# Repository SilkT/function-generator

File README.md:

# function-generator
A function generator with variable frequency and different typical signals to choose from(sine, triangle, saw and square).
the project is based on STM32F051K8 microcontroller which features built-in DAC. Shematics and layout were designed using Autodesk Eagle software. For the most part shematics were designed according to datasheets of used components. The resulting analog signal is ‘cleaned’ from high frequency component with calculated passive low-pass filter.
Software part of the project was executed in C using STM32Cube for configuration and Keil µVision as IDE. Project uses standard HAL drivers and own code for digital-to-analog processing with wavetables generated in Matlab, that are converted to analog values on the output of device. Modified OpenSource library is used for indication on the OLED screen.
Software still needs a lot of tuning, but that's just a part of a bigger project involving DSP on low-end STM32 MCUs so I'm working on it ;)

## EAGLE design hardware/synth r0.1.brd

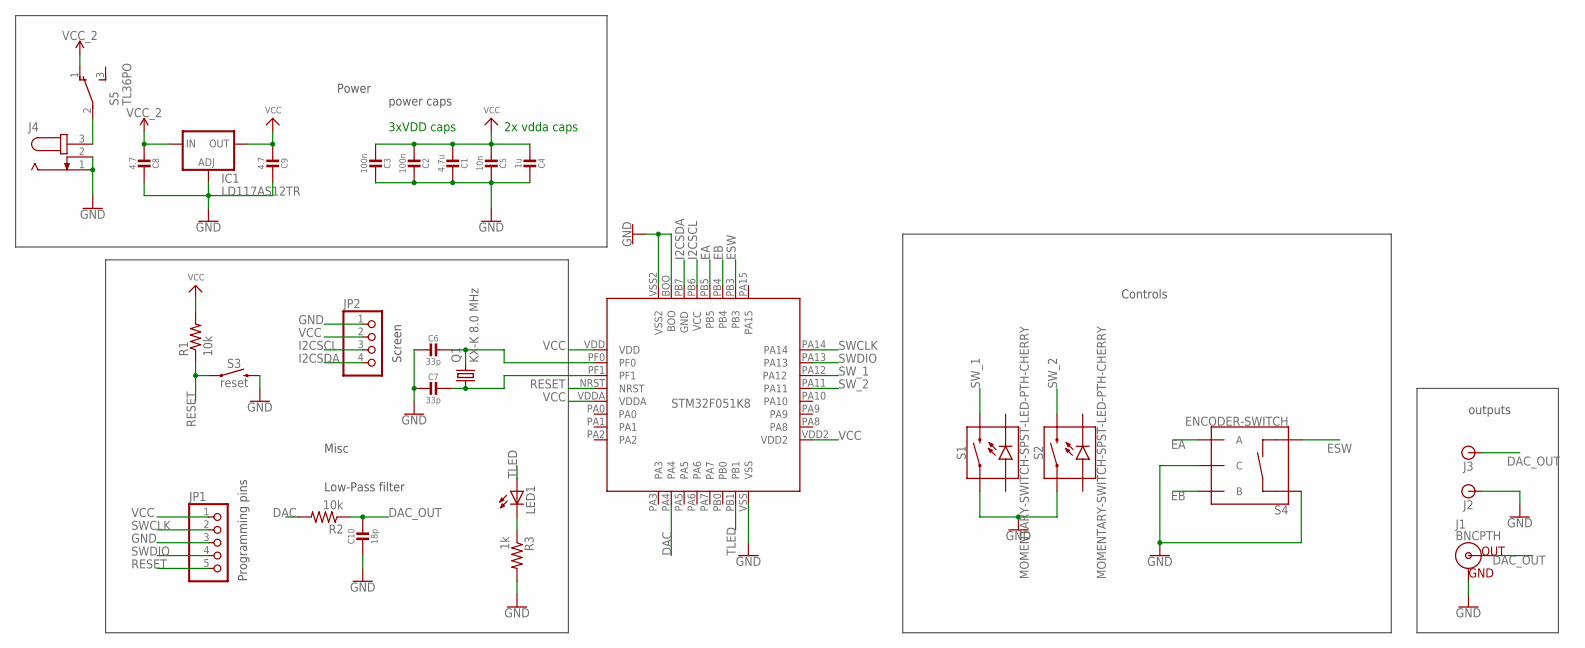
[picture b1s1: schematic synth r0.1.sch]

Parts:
C1: 4.7u; 0805-NO
C2, C3: 100n; 0805-NO
C4: 1u; 0805-NO
C5: 10n; 0805-NO
C6, C7: 33p; 0805-NO
C8, C9: 4.7; 0805-NO
C10: 18p; 0805-NO
IC1: LD117AS12TR; SOT223
J1: BNCPTH; BNC
J2, J3: BANANA_CONN
J4: JACK-PLUG1; SPC4078
JP1: PINHD-1X5; 1X05
JP2: PINHD-1X4; 1X04
LED1: LEDCHIPLED_0805; CHIPLED_0805
Q1: KX-K 8.0 MHz; HC49/S
R1, R2: 10k; R0805
R3: 1k; R0805
S1, S2: MOMENTARY-SWITCH-SPST-LED-PTH-CHERRY; CHERRY-MX-LED
S3: reset; TACTILE_SWITCH_SMD_5.2MM
S4: ENCODER-SWITCH; ROTARY_ENC_PLAIN
S5: TL36PO; TL3XPO
U$1: STM32F051K8; LQFP32-7X7

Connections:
DAC: R2.2, U$1.PA4
DAC_OUT: C10.1, J1.S (OUT), J3.P$1, R2.1
EA: S4.A, U$1.PB5
EB: S4.B, U$1.PB4
ESW: S4.SW-, U$1.PB3
GND: C1.1, C2.1, C3.1, C4.1, C5.1, C6.2, C7.2, C8.1, C9.1, C10.2, IC1.1 (ADJ), J1.GND, J2.P$1, J4.1, J4.2, JP1.3, JP2.1, R3.2, S1.S1 (1), S2.S1 (1), S3.3 (2), S3.4 (2), S4.C, S4.SW+, U$1.BOO, U$1.VSS, U$1.VSS2
I2CSCL: JP2.3, U$1.PB6
I2CSDA: JP2.4, U$1.PB7
unnamed: C6.1, Q1.2, U$1.PF0
unnamed: C7.1, Q1.1, U$1.PF1
unnamed: J4.3, S5.2
unnamed: LED1.C, R3.1
PA0: U$1.PA0
PA7: U$1.PA7
PB0: U$1.PB0
RESET: JP1.5, R1.1, S3.1, S3.2 (1), U$1.NRST
SWCLK: JP1.2, U$1.PA14
SWDIO: JP1.4, U$1.PA13
SW_1: S1.S2 (2), U$1.PA12
SW_2: S2.S2 (2), U$1.PA11
TLED: LED1.A, U$1.PB1
VCC: C1.2, C2.2, C3.2, C4.2, C5.2, C9.2, IC1.4 (OUT), JP1.1, JP2.2, R1.2, U$1.VDD, U$1.VDD2, U$1.VDDA
VCC_2: C8.2, IC1.3 (IN), S5.1 (O)

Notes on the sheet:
3xVDD caps
2x vdda caps
power caps
Power
outputs
Misc
Controls
Programming pins
Low-Pass filter
Screen

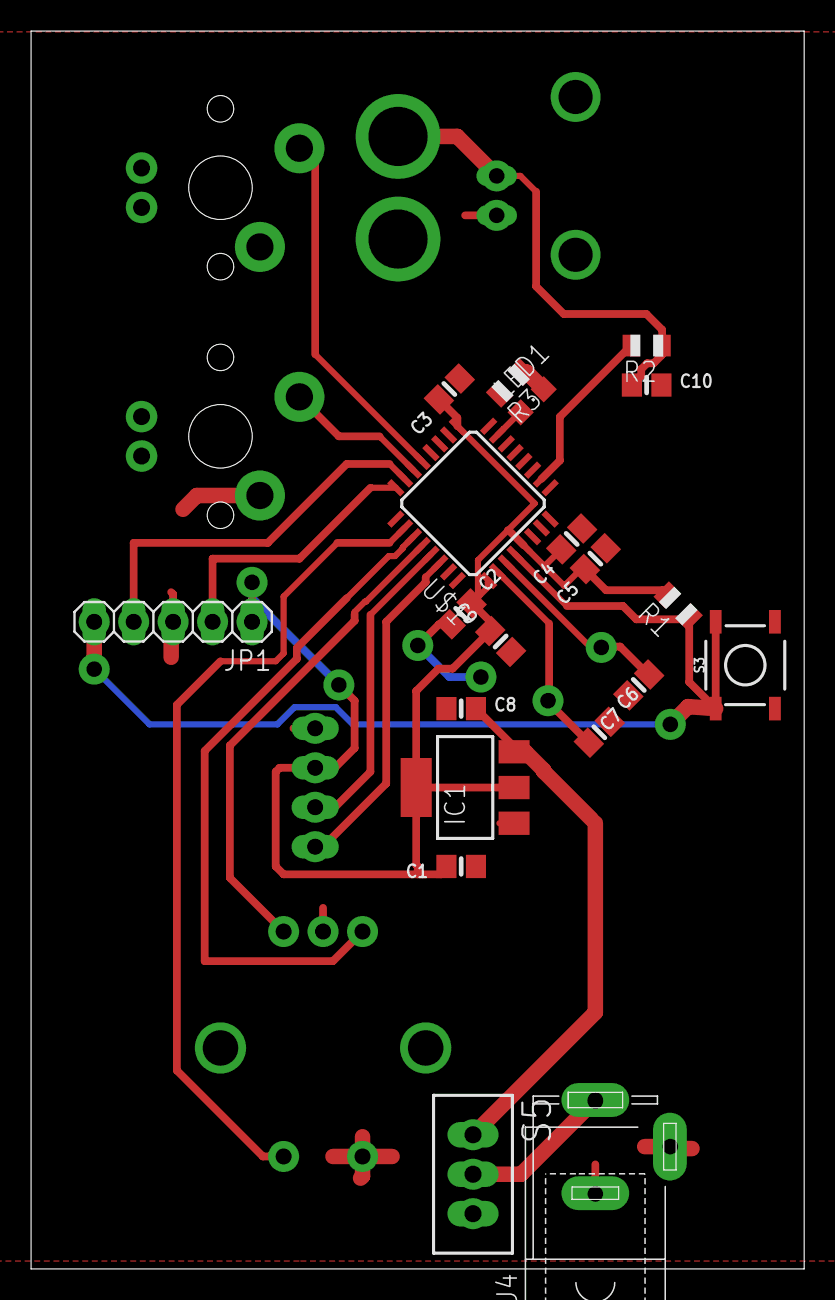
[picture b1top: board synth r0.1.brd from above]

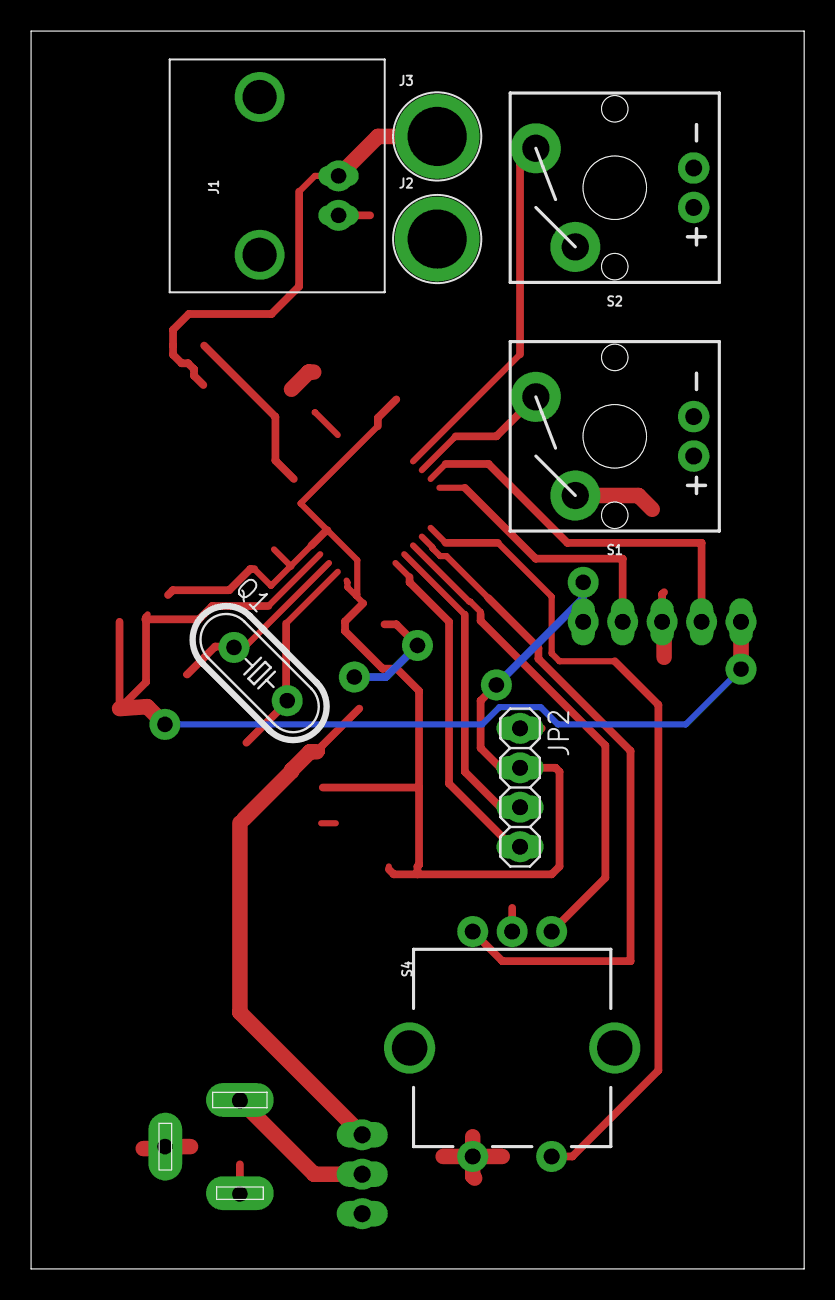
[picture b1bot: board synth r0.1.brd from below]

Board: 2 copper layers, 49.8 x 79.7 mm, 28 parts (8 on the bottom side), 20 nets.

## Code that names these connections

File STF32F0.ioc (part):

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Mcu.Name=STM32F051K8Tx
Mcu.Package=LQFP32
Mcu.UserName=STM32F051K8Tx
PA11.GPIOParameters=GPIO_PuPd
PA11.GPIO_PuPd=GPIO_PULLUP
PA11.Signal=GPIO_Input
PA12.GPIOParameters=GPIO_PuPd
PA12.GPIO_PuPd=GPIO_PULLUP
PA12.Signal=GPIO_Input
PA13.Mode=Serial_Wire
PA13.Signal=SYS_SWDIO
PA14.Mode=Serial_Wire
PA14.Signal=SYS_SWCLK
PA4.Signal=COMP_DAC11_group
PB1.Signal=GPIO_Output
PB3.GPIOParameters=GPIO_PuPd
PB3.GPIO_PuPd=GPIO_PULLUP
PB3.Signal=GPIO_Input
PB4.GPIOParameters=GPIO_PuPd
PB4.GPIO_PuPd=GPIO_PULLUP
PB4.Signal=GPIO_Input
PB5.GPIOParameters=GPIO_PuPd
PB5.GPIO_PuPd=GPIO_PULLUP
PB5.Signal=GPIO_Input
PB6.GPIOParameters=GPIO_Speed,GPIO_FM6,GPIO_PuPdOD
PB6.GPIO_FM6=SYSCFG_CFGR1_I2C_FMP_PB6
PB6.GPIO_PuPdOD=GPIO_PULLUP
PB6.GPIO_Speed=GPIO_SPEED_FREQ_HIGH
PB6.Mode=I2C
PB6.Signal=I2C1_SCL
PB7.GPIOParameters=GPIO_FM7
PB7.GPIO_FM7=SYSCFG_CFGR1_I2C_FMP_PB7
PB7.Mode=I2C
PB7.Signal=I2C1_SDA
PF0-OSC_IN.Mode=HSE-External-Oscillator
PF0-OSC_IN.Signal=RCC_OSC_IN
PF1-OSC_OUT.Mode=HSE-External-Oscillator
PF1-OSC_OUT.Signal=RCC_OSC_OUT
RCC.SYSCLKFreq_VALUE=48000000
RCC.SYSCLKSource=RCC_SYSCLKSOURCE_PLLCLK
board=custom

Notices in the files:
parts and their libraries:
SparkFun-Connectors: Licensing: Creative Commons ShareAlike 4.0 International - https://creativecommons.org/licenses/by-sa/4.0
